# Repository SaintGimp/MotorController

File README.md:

# MotorController

The board files use the libraries and design rules from https://github.com/SaintGimp/Eagle.

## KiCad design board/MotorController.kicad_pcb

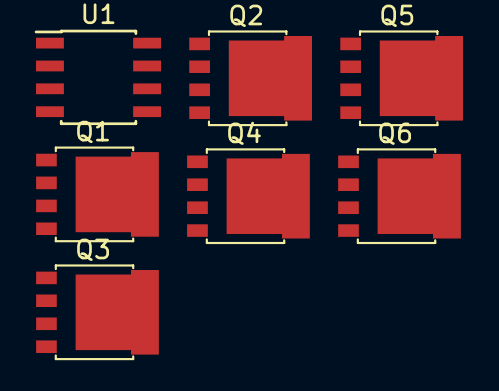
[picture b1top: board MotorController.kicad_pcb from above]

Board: 2 copper layers, 7 parts (0 on the bottom side), 5 nets, no tracks yet.

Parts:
Q1, Q2, Q3, Q4, Q5, Q6: PSMN5R5-60YS; LFPAK56
U1: MIC4605-1YM; SOIC-8_3.9x4.9mm_P1.27mm

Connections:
+24V: Q1.5, Q3.5, Q5.5
/PowerStage/U_PHASE: Q1.1, Q1.2, Q1.3, Q2.5
/PowerStage/V_PHASE: Q3.1, Q3.2, Q3.3, Q4.5
/PowerStage/W_PHASE: Q5.1, Q5.2, Q5.3, Q6.5
unnamed: Q2.1, Q2.2, Q2.3, Q4.1, Q4.2, Q4.3, Q6.1, Q6.2, Q6.3

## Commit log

2013-12-04 One pot controlling speed output
2013-12-05 Added rate pot, on/off and direction switches
2013-12-07 Support ATTiny84 and ATTiny85 MCUs
2013-12-07 Arduino-tiny core for ATTiny MCUs
2013-12-07 Tweaks
2013-12-07 Assume that ATTiny85 is going to need RESET disabled
2013-12-10 Fixed PWM output and renamed sketch
2013-12-10 Tweaked speed minimum and ramp min/max to match specs
2013-12-14 Include Eagle design files and move stuff around
2013-12-14 Add a ground pour on the bottom plane and route all power and signal traces on the top
2013-12-14 Tweaked schematic
2013-12-14 Switch to a top GND pour
2013-12-14 Switch to a horizontal regulator and change board layout to fit
2013-12-14 License file
2013-12-28 Board tweaks, prototype labels
2013-12-28 Only allow power on if current speed is 0
2014-01-02 Parameter tweaks based on prototype trials
2014-01-02 Add RPM display and move to ATTiny84
2014-01-03 Change RPM calculation to expect one pulse every 90 deg of rotation
2014-04-13 V2 prototype
2014-04-17 Initial pass at a PCB and added clock code
2014-04-28 PCB improvements
2015-04-08 Update with current design rules and current library
2015-04-08 Pull up reset line
2015-04-09 Replace I2C with serial library
2015-04-11 Refit LCDi2cNHD library for serial
2015-04-11 Stop at zero speed when changing direction rather than starting up again
2015-05-26 New board layout
2015-05-26 Restore resistor values
2015-05-26 Add dimensions
2015-05-28 Board tweaks
2015-05-28 Board layout improvements
2015-05-28 Fix position of D3 label
2015-05-29 Remove old libraries and design files
2015-05-29 Remove old prototype files
2015-05-29 Add readme
2015-06-06 Change triac value
2015-06-06 Updated BOM
2015-07-10 Fix power input labels and increase isolation for ground plane
2015-07-10 Oversample the speed pot. Even better would be to have true hysteresis.
2015-07-10 More BOM updates
2015-07-13 Start front panel board
2015-07-13 Switch to pin headers and ATMega328P
2015-07-13 Double the maximum delay for ramp
2015-07-18 Version 3, many changes
2015-07-18 Add soft-start capability to avoid high inrush current
2015-07-25 Remove unneeded file
2015-07-25 Front panel design with dimension markings
2015-07-25 Many changes for version 3
2015-07-25 Clean up front panel
2015-07-25 Front panel tweaks
2015-07-27 Miter corners of control board
2015-07-27 Adjust front panel layout
2015-07-27 Spread out front panel buttons, flip terminal silkscreen to back
2015-07-29 Improve bypass cap layout
2015-07-29 Adjust spacing of DAC filter and ICSP header
2015-07-29 Adjust clearance of MCU power trace
2015-07-29 Revert MCU power trace
2015-07-29 Tweak label
2015-08-08 Tweak TO220 packages and add board heatsink
2015-08-08 Fix the label order of caps
2015-08-08 More adjustments to BOM and parts labels
2015-08-15 Even more BOM and label adjustments
2015-08-16 Update firmware to ATMega328P and add stop damping
2015-08-16 Revert back to previous triac circuit
2015-08-16 Connect RPM IN to pin 5 which supports interrupts
2015-08-16 Bump board version
2015-08-28 Tweak mask settings in design rules
2015-08-28 Bump patch version
2015-10-27 Update DRU for front panel and bump version
2015-10-27 Update library and DRU for main board
2015-10-28 Switched to 60V MOSFETs and updated BOM and inventory
2015-11-14 Add installation files for Windows and delete unused libraries
2015-11-15 Add pause at the end of install script and add test procedures doc
2016-07-06 Add the ability to reset the clock by shorting EXP3 and toggle debug display by shorting EXP2
2016-07-06 Add hole to front panel
2016-07-06 Update inventory
2016-07-06 Firmware version 3.1.0
2016-08-11 Switch to the Bounce2 library
2016-08-11 Remove delay from main loop and control motor updates with a specific delay
2016-08-11 Convert periodic tasks to use ArduinoThread library
2016-08-14 Add libraries as direct project files so we always have the correct versions
2016-08-15 Shrink the loop time by not multisampling the ramp pot, which doesn't need it
2016-08-15 Firmware version 3.1.1
2016-09-12 Updated inventory
2016-10-06 Debug firmware to troubleshoot clock problems
2016-10-06 Fix clock bug on debug branch
2016-10-06 Fix an off-by-one bug in the way we load clock values
2016-10-06 Firmware 3.1.2
2016-10-06 Final fix on debug branch
2017-09-15 Update stock
2019-05-02 Fix a missing line in board outline and generate JCLPCB gerbers
2019-05-02 Updated test procedures
2019-05-02 Updated stock levels
2020-01-09 Initial commit of V2 code
2020-01-09 vNext redesign WIP
2022-05-07 Update BOM and test procedures
2022-05-11 Test doc updates
2022-09-20 Fix overflow bug in hours display
2022-09-20 Add new 3.1.3 firmware and update script files
2023-08-21 Changes to support RioRand motor driver module
2023-08-21 Firmware 4.0.0 and updated install scripts
